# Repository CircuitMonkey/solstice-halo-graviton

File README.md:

# solstice-halo-graviton
16-channel vibrator/small-motor driver board that uses the TLC59401 PWM chip.

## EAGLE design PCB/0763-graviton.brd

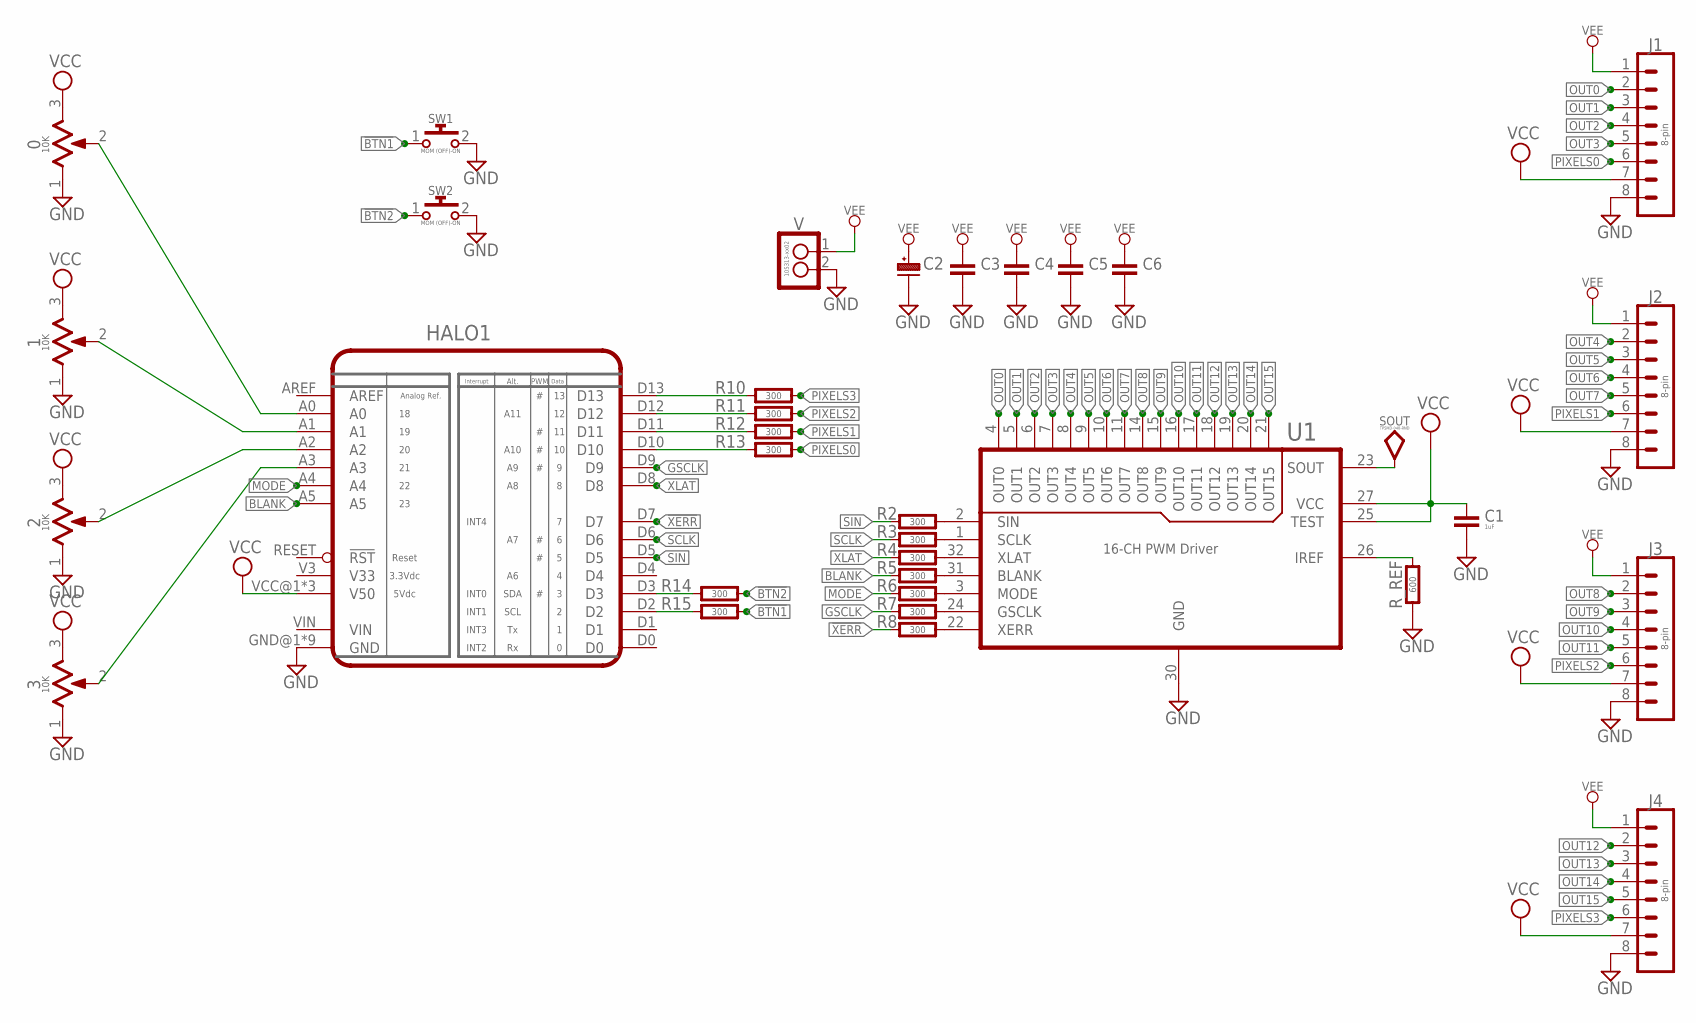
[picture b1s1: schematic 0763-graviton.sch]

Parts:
0, 1, 2, 3: 10K; ALPS_RK09D113
C1: 1uF; 0603-CAP
C2: CAPACITOR_POL-ALUM-SMT-10; CAP_ALUM_SMT_10
C3, C4, C5, C6: CAPACITOR1210; 1210-CAP
HALO1: HALO-A2; PCB-HALO-A2-PINS
J1, J2, J3, J4: 8-pin; B8B-PH-SM4
R2, R3, R4, R5, R6, R7, R8, R10, R11, R12, R13, R14, R15: 300; 0603-RES
R_REF: 600; 0603-RES
SOUT: TPSMD-040-RND; SMD-040MIL-RND
SW1, SW2: MOM (OFF)-ON; SWITCH-0635-2P-SMD
U1: 16-CH PWM Driver; QFN-32
V: 105313-xx02; MOLEX-105313-XX02

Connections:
!BTN1: R15.1, SW1.1
!BTN2: R14.1, SW2.1
!XERR: HALO1.D7, R8.2
BLANK: HALO1.A5, R5.2
GND: 0.1, 0.MT1A (GND), 0.MT1B (GND), 0.MT1C (GND), 0.MT2A (GND), 0.MT2B (GND), 0.MT2C (GND), 1.1, 1.MT1A (GND), 1.MT1B (GND), 1.MT1C (GND), 1.MT2A (GND), 1.MT2B (GND), 1.MT2C (GND), 2.1, 2.MT1A (GND), 2.MT1B (GND), 2.MT1C (GND), 2.MT2A (GND), 2.MT2B (GND), 2.MT2C (GND), 3.1, 3.MT1A (GND), 3.MT1B (GND), 3.MT1C (GND), 3.MT2A (GND), 3.MT2B (GND), 3.MT2C (GND), C1.2, C2.- (N), C3.2, C4.2, C5.2, C6.2, HALO1.GND@1 (GND), HALO1.GND@1.2 (GND), HALO1.GND@2 (GND), HALO1.GND@3 (GND), HALO1.GND@4 (GND), HALO1.MTG1 (GND), HALO1.MTG2 (GND), HALO1.MTG3 (GND), HALO1.MTG4 (GND), J1.8, J2.8, J3.8, J4.8, R_REF.1, SW1.2, SW2.2, U1.30 (GND), V.2
GSCLK: HALO1.D9, R7.2
MODE: HALO1.A4, R6.2
unnamed: HALO1.D13, R10.2
unnamed: HALO1.D12, R11.2
unnamed: R_REF.2, U1.26 (IREF)
unnamed: R2.1, U1.2 (SIN)
unnamed: R3.1, U1.1 (SCLK)
unnamed: R4.1, U1.32 (XLAT)
unnamed: R5.1, U1.31 (BLANK)
unnamed: R6.1, U1.3 (MODE)
unnamed: R7.1, U1.24 (GSCLK)
unnamed: R8.1, U1.22 (XERR)
unnamed: HALO1.D11, R12.2
unnamed: HALO1.D10, R13.2
unnamed: 0.2, HALO1.A0
unnamed: 1.2, HALO1.A1
unnamed: 2.2, HALO1.A2
unnamed: 3.2, HALO1.A3
unnamed: HALO1.D3, R14.2
unnamed: HALO1.D2, R15.2
OUT0: J1.2, U1.4 (OUT0)
OUT1: J1.3, U1.5 (OUT1)
OUT2: J1.4, U1.6 (OUT2)
OUT3: J1.5, U1.7 (OUT3)
OUT4: J2.2, U1.8 (OUT4)
OUT5: J2.3, U1.9 (OUT5)
OUT6: J2.4, U1.10 (OUT6)
OUT7: J2.5, U1.11 (OUT7)
OUT8: J3.2, U1.14 (OUT8)
OUT9: J3.3, U1.15 (OUT9)
OUT10: J3.4, U1.16 (OUT10)
OUT11: J3.5, U1.17 (OUT11)
OUT12: J4.2, U1.18 (OUT12)
OUT13: J4.3, U1.19 (OUT13)
OUT14: J4.4, U1.20 (OUT14)
OUT15: J4.5, U1.21 (OUT15)
PIXELS0: J1.6, R13.1
PIXELS1: J2.6, R12.1
PIXELS2: J3.6, R11.1
PIXELS3: J4.6, R10.1
SCLK: HALO1.D6, R3.2
SIN: HALO1.D5, R2.2
SOUT: SOUT.TP, U1.23 (SOUT)
VCC: 0.3, 1.3, 2.3, 3.3, C1.1, HALO1.VCC@1 (V50), HALO1.VCC@2 (V50), HALO1.VCC@3 (V50), J1.7, J2.7, J3.7, J4.7, U1.25 (TEST), U1.27 (VCC)
VEE: C2.+, C3.1, C4.1, C5.1, C6.1, J1.1, J2.1, J3.1, J4.1, V.1
XLAT: HALO1.D8, R4.2

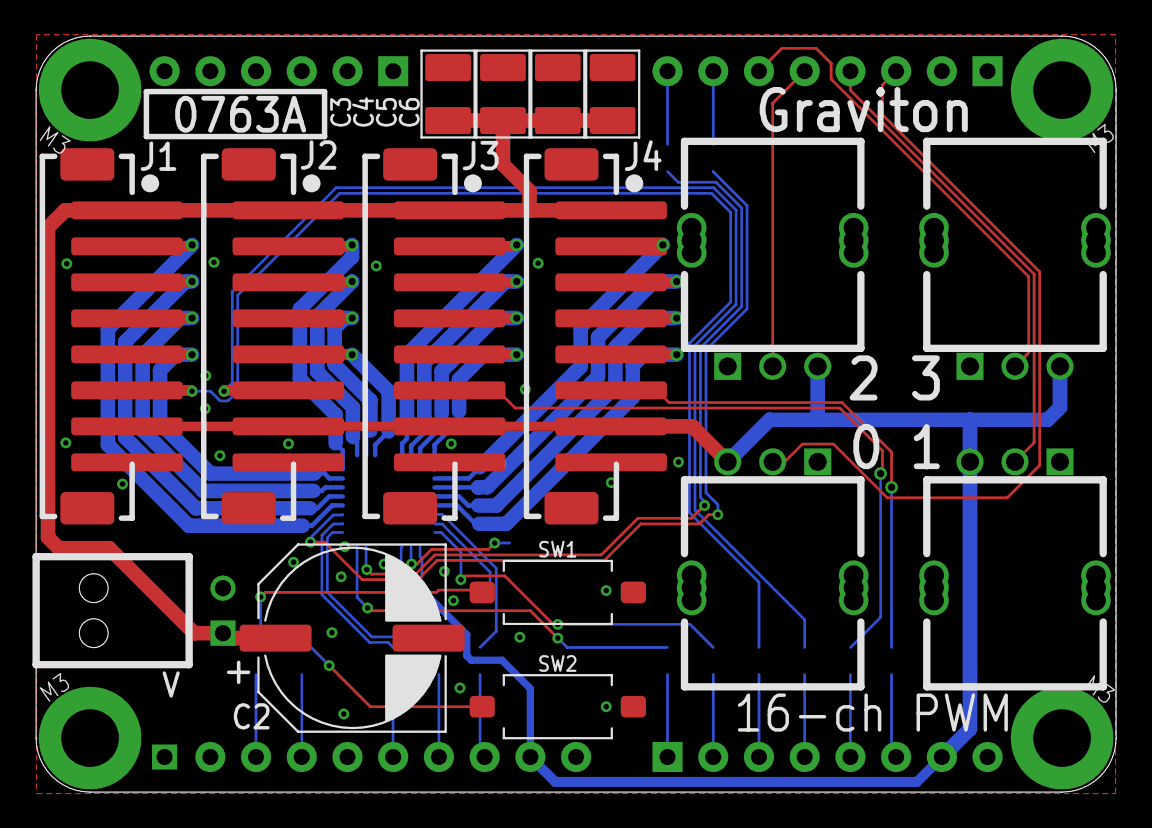
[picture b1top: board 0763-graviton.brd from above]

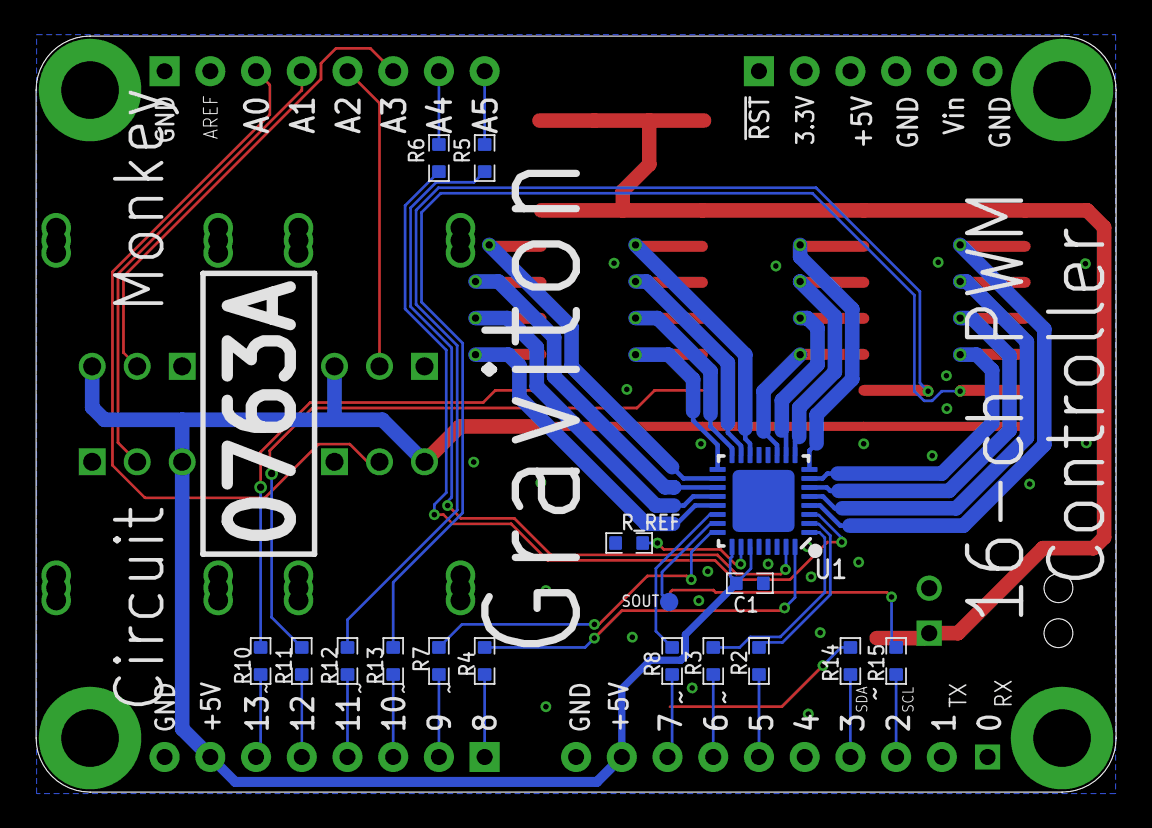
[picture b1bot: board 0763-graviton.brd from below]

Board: 2 copper layers, 60.0 x 42.0 mm, 34 parts (17 on the bottom side), 51 nets.

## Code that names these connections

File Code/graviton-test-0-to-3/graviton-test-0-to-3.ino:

/*
 
 */
#include "TLC59401.h"
#include <Adafruit_NeoPixel.h>
#ifdef __AVR__
  #include <avr/power.h>
#endif

#define BTN1  2
#define BTN2  3

// Halo for Rev. A is incorrect A5 to A0 are reversed
// Rev. A
#define POT0 A5
#define POT1 A4
#define POT2 A3
#define POT3 A2

// Rev. B
//#define POT0 A0
//#define POT1 A1
//#define POT2 A2
//#define POT3 A3

#define PIXELS0 10
#define PIXELS1 11
#define PIXELS2 12
#define PIXELS3 13

// Rev. B
//#define MODE  A4
//#define BLANK A5

// Rev. A
#define MODE  A1
#define BLANK A0

#define GSCLK  9
#define XLAT   8
#define SCLK   6
#define SIN    5

TLC59401 vibes = TLC59401(MODE, BLANK, GSCLK, XLAT, SCLK, SIN );

Adafruit_NeoPixel strip0 = Adafruit_NeoPixel(4, PIXELS0, NEO_GRB + NEO_KHZ800);

int potValue0 = 0;  // variable to store the value coming from the sensor
int potValue1 = 0;  // variable to store the value coming from the sensor
int potValue2 = 0;  // variable to store the value coming from the sensor
int potValue3 = 0;  // variable to store the value coming from the sensor

void setup() {
//  Serial.begin(9600);
//  while (!Serial) {}

  vibes.begin();
  vibes.push();
  vibes.blank(0);
  
  strip0.begin();
  strip0.show(); // Initialize all pixels to 'off'
}

void loop() {
  // read the value from the sensor:
  potValue0 = analogRead(POT0);
  potValue1 = analogRead(POT1);
  potValue2 = analogRead(POT2);
  potValue3 = analogRead(POT3);

//  strip0.setPixelColor(0, Wheel(potValue0/4) );
//  strip0.setPixelColor(1, Wheel(potValue1/4) );
//  strip0.setPixelColor(2, Wheel(potValue2/4) );
//  strip0.setPixelColor(3, Wheel(potValue3/4) );
  strip0.setPixelColor(0, potValue0/4, 0, 0 );
  strip0.setPixelColor(1, potValue1/4, 0, 0 );
  strip0.setPixelColor(2, potValue2/4, 0, 0 );
  strip0.setPixelColor(3, potValue3/4, 0, 0 );
  strip0.show();

  vibes.set( 0, potValue0<<2 );  // Shift 10-bit analog read to 12-bit stored value.
  vibes.set( 1, potValue1<<2 );
  vibes.set( 2, potValue2<<2 );
  vibes.set( 3, potValue3<<2 );
  
  vibes.push();
  
//  Serial.print( potValue0 );
//  Serial.print( " " );
//  Serial.print( potValue1 );
//  Serial.print( " " );
//  Serial.print( potValue2 );
//  Serial.print( " " );
//  Serial.print( potValue3 );
//  Serial.print( " " );
//  Serial.print("\n");

  //delay(50);
}

// Input a value 0 to 255 to get a color value.
// The colours are a transition r - g - b - back to r.
uint32_t Wheel(byte WheelPos) {
  WheelPos = 255 - WheelPos;
  if(WheelPos < 85) {
    return strip0.Color(255 - WheelPos * 3, 0, WheelPos * 3);
  }
  if(WheelPos < 170) {
    WheelPos -= 85;
    return strip0.Color(0, WheelPos * 3, 255 - WheelPos * 3);
  }
  WheelPos -= 170;
  return strip0.Color(WheelPos * 3, 255 - WheelPos * 3, 0);
}

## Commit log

2020-04-26 Initial commit of Graviton PCB with test code.
2021-07-29 Graviton progress
2023-04-23 Add redline-sch and top place.
